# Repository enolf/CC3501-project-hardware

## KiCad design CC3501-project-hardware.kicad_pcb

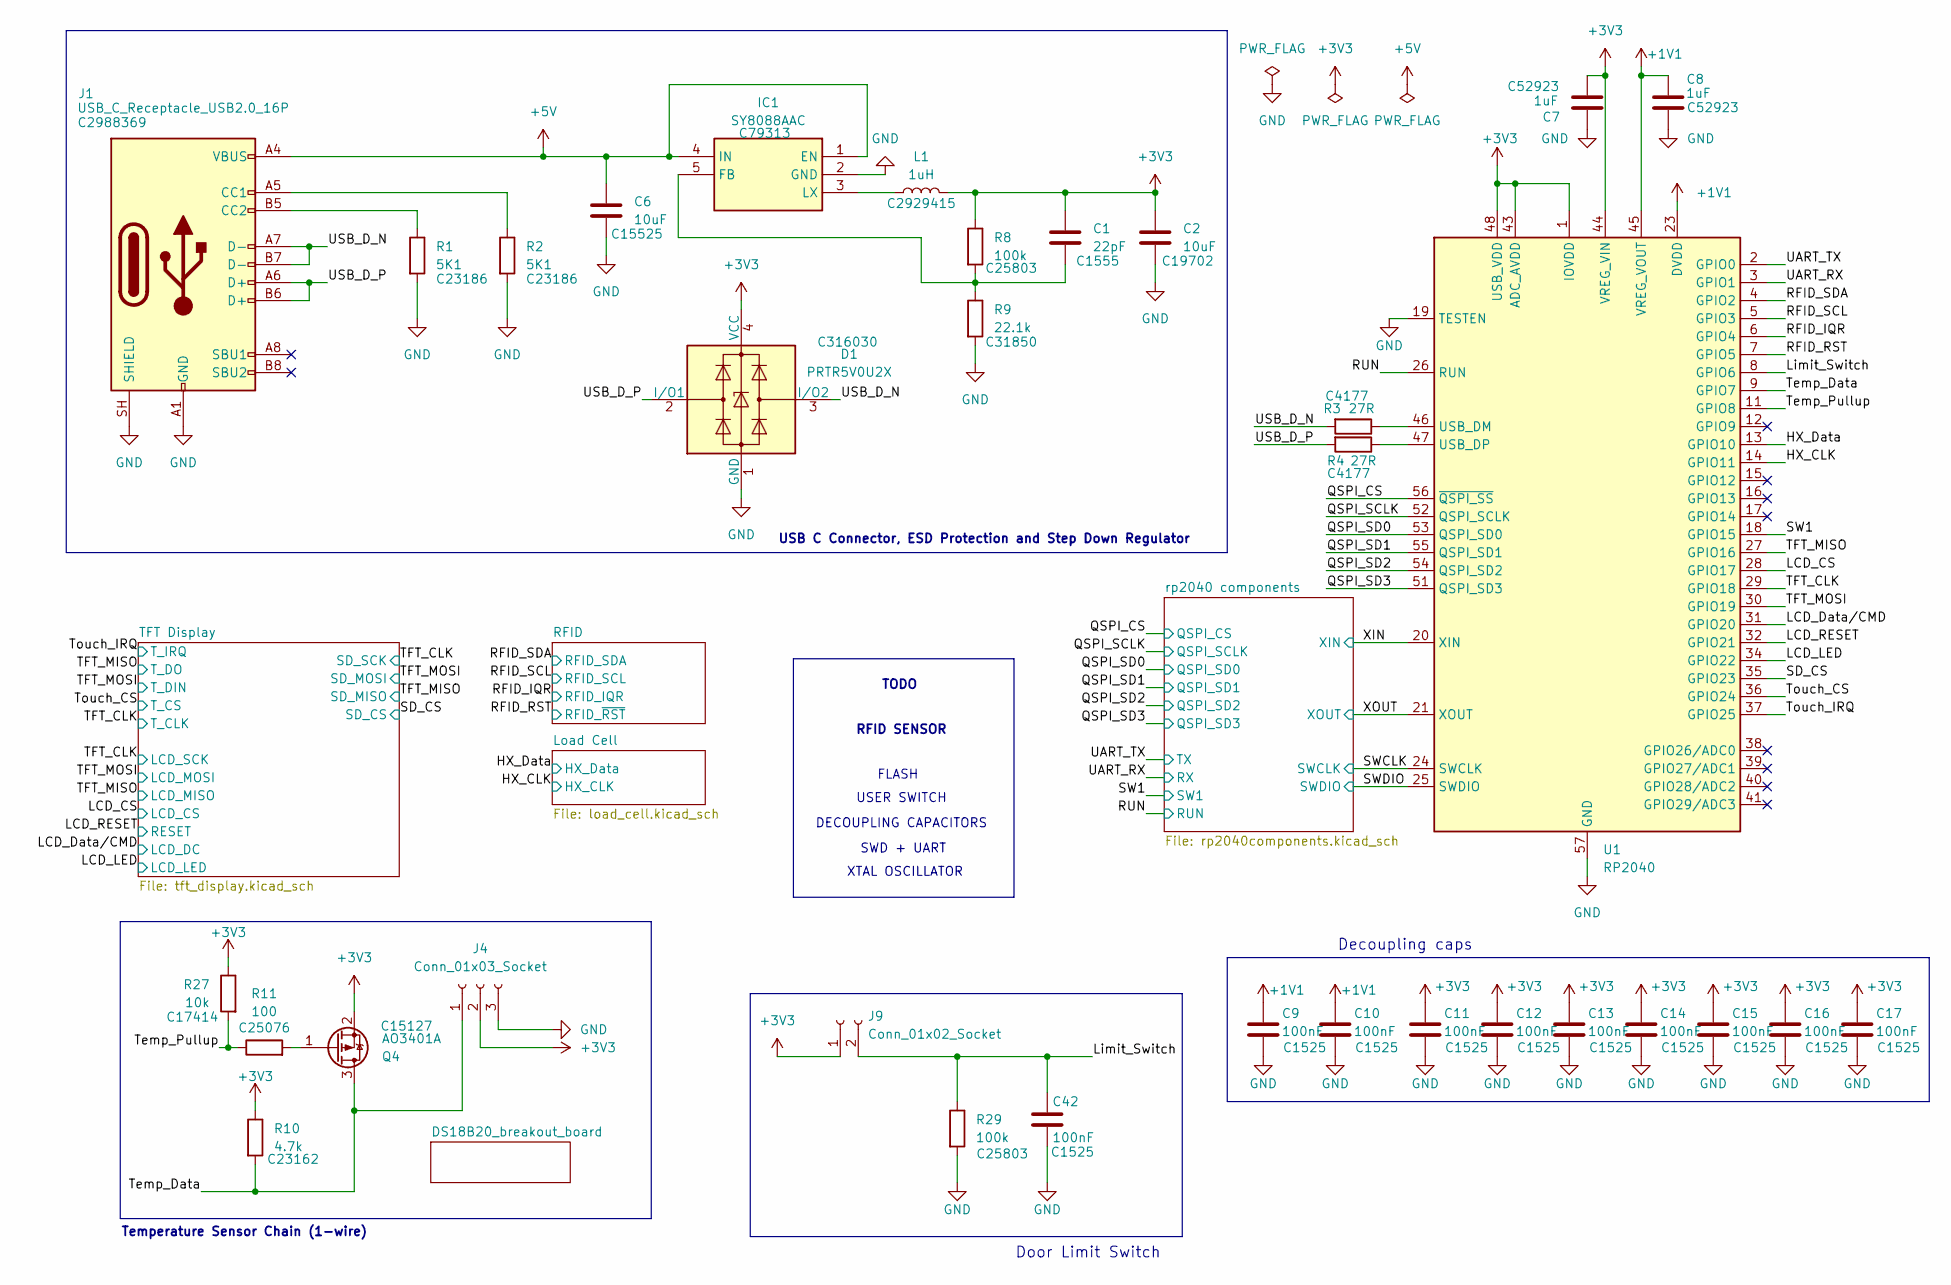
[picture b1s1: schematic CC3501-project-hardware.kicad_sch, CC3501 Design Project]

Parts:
C1: 22pF; C_0402_1005Metric; LCSC PN C1555
C2: 10uF; C_0603_1608Metric; LCSC PN C19702
C6: 10uF; C_0402_1005Metric; LCSC PN C15525
C7, C8: 1uF; C_0402_1005Metric; LCSC PN C52923
C9, C10, C11, C12, C13, C14, C15, C16, C17, C42: 100nF; C_0402_1005Metric; LCSC PN C1525
D1: PRTR5V0U2X; SOT-143; LCSC PN C316030
IC1: SY8088AAC; SOT95P285X140-5N; Manufacturer_Part_Number SY8088AAC
J1: USB_C_Receptacle_USB2.0_16P; USB_C_Receptacle_G-Switch_GT-USB-7010ASV; LCSC PN C2988369
J4: Conn_01x03_Socket; PinHeader_1x03_P2.54mm_Vertical
J9: Conn_01x02_Socket; PinHeader_1x02_P2.54mm_Vertical
L1: 1uH; IND-SMD_L4.5-W4.0; LCSC PN C2929415
Q4: AO3401A; SOT-23; LCSC PN C15127
R1, R2: 5K1; R_0201_0603Metric; LCSC PN C23186
R3, R4: 27R; R_0603_1608Metric; LCSC PN C4177
R8, R29: 100k; R_0603_1608Metric; LCSC PN C25803
R9: 22.1k; R_0603_1608Metric; LCSC PN C31850
R10: 4.7k; R_0603_1608Metric; LCSC PN C23162
R11: 100; R_0402_1005Metric; LCSC PN C25076
R27: 10k; R_0805_2012Metric; LCSC PN C17414
U1: RP2040; QFN-56-1EP_7x7mm_P0.4mm_EP3.2x3.2mm; LCSC PN C2040

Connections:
+1V1: C8.2, C9.1, C10.1, U1.23 (DVDD), U1.45 (VREG_VOUT), U1.50 (DVDD)
+5V: C6.1, IC1.1 (EN), IC1.4 (IN), J1.A4 (VBUS), J1.A9 (VBUS), J1.B4 (VBUS), J1.B9 (VBUS); also elsewhere on the board
/HX_CLK: U1.14 (GPIO11); also elsewhere on the board
/HX_Data: U1.13 (GPIO10); also elsewhere on the board
/LCD_CS: U1.28 (GPIO17); also elsewhere on the board
/LCD_Data/CMD: U1.31 (GPIO20); also elsewhere on the board
/LCD_LED: U1.34 (GPIO22); also elsewhere on the board
/LCD_RESET: U1.32 (GPIO21); also elsewhere on the board
/Limit_Switch: C42.1, J9.2, R29.1, U1.8 (GPIO6)
/QSPI_CS: U1.56 (~QSPI_SS); also elsewhere on the board
/QSPI_SCLK: U1.52 (QSPI_SCLK); also elsewhere on the board
/QSPI_SD0: U1.53 (QSPI_SD0); also elsewhere on the board
/QSPI_SD1: U1.55 (QSPI_SD1); also elsewhere on the board
/QSPI_SD2: U1.54 (QSPI_SD2); also elsewhere on the board
/QSPI_SD3: U1.51 (QSPI_SD3); also elsewhere on the board
/RFID_IQR: U1.6 (GPIO4); also elsewhere on the board
/RFID_RST: U1.7 (GPIO5); also elsewhere on the board
/RFID_SCL: U1.5 (GPIO3); also elsewhere on the board
/RFID_SDA: U1.4 (GPIO2); also elsewhere on the board
/RUN: U1.26 (RUN); also elsewhere on the board
/SD_CS: U1.35 (GPIO23); also elsewhere on the board
/SW1: U1.18 (GPIO15); also elsewhere on the board
/SWCLK: U1.24 (SWCLK); also elsewhere on the board
/SWDIO: U1.25 (SWDIO); also elsewhere on the board
/TFT_CLK: U1.29 (GPIO18); also elsewhere on the board
/TFT_MISO: U1.27 (GPIO16); also elsewhere on the board
/TFT_MOSI: U1.30 (GPIO19); also elsewhere on the board
/Temp_Data: J4.1, Q4.3 (D), R10.2, U1.9 (GPIO7)
/Temp_Pullup: R11.1, R27.2, U1.11 (GPIO8)
/Touch_CS: U1.36 (GPIO24); also elsewhere on the board
/Touch_IRQ: U1.37 (GPIO25); also elsewhere on the board
/USB_D_N: D1.3 (I/O2), J1.A7 (D-), J1.B7 (D-), R3.2
/USB_D_P: D1.2 (I/O1), J1.A6 (D+), J1.B6 (D+), R4.2
/XIN: U1.20 (XIN); also elsewhere on the board
/XOUT: U1.21 (XOUT); also elsewhere on the board
GND: C2.2, C6.2, C7.1, C8.1, C9.2, C10.2, C11.2, C12.2, C13.2, C14.2, C15.2, C16.2, C17.2, C42.2, D1.1 (GND), IC1.2 (GND), J1.A1 (GND), J1.A12 (GND), J1.B1 (GND), J1.B12 (GND), J1.SH (SHIELD), J4.3, R1.2, R2.2, R9.2, R29.2, U1.19 (TESTEN), U1.57 (GND); also elsewhere on the board
unnamed: C1.2, IC1.5 (FB), R8.2, R9.1
unnamed: IC1.3 (LX), L1.2
unnamed: J1.A5 (CC1), R2.1
unnamed: J1.B5 (CC2), R1.1
unnamed: Q4.1 (G), R11.2
unnamed: R3.1, U1.46 (USB_DM)
unnamed: R4.1, U1.47 (USB_DP)

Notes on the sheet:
TODO
FLASH
DECOUPLING CAPACITORS
Door Limit Switch
Decoupling caps
RFID SENSOR
SWD + UART
XTAL OSCILLATOR
USB C Connector, ESD Protection and Step Down Regulator
USER SWITCH
Temperature Sensor Chain (1-wire)

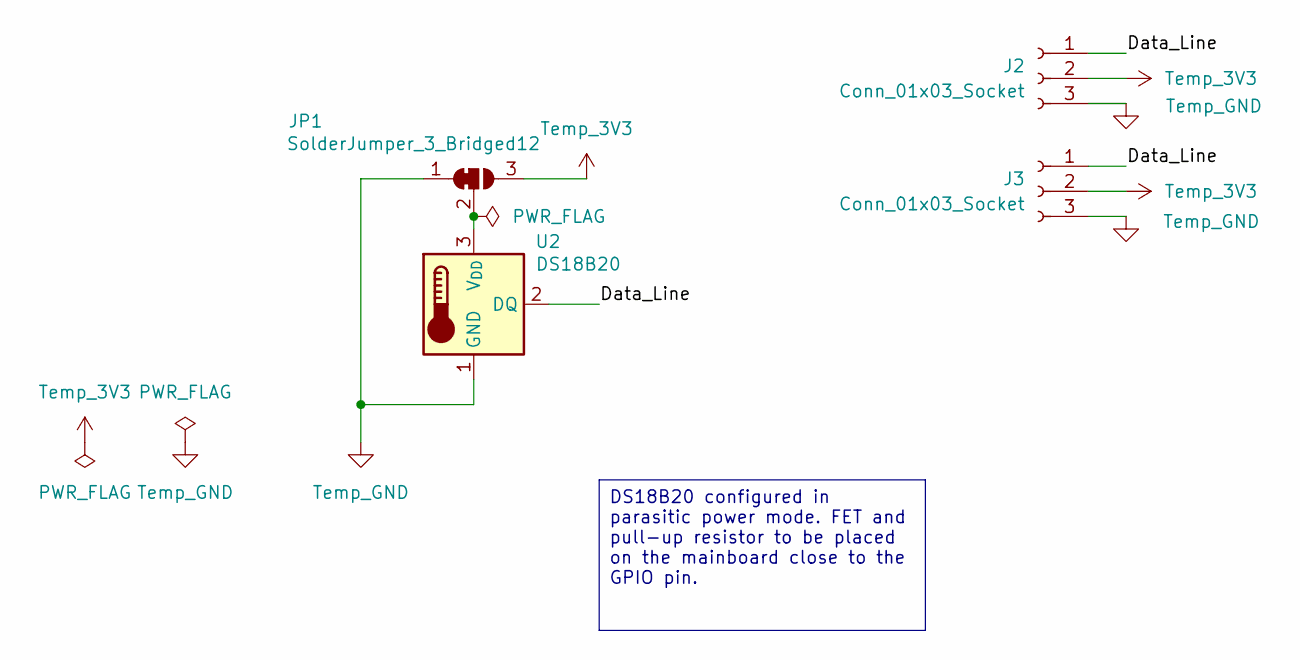
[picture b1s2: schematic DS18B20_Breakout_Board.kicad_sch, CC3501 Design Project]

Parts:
J2, J3: Conn_01x03_Socket; PinSocket_1x03_P2.54mm_Vertical
JP1: SolderJumper_3_Bridged12; SolderJumper-3_P1.3mm_Bridged12_RoundedPad1.0x1.5mm_NumberL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
U2: DS18B20; TO-92_Inline

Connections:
Temp_3V3: J2.2, J3.2, JP1.3 (B)

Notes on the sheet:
DS18B20 configured in parasitic power mode. FET and pull-up resistor to be placed on the mainboard close to the GPIO pin.

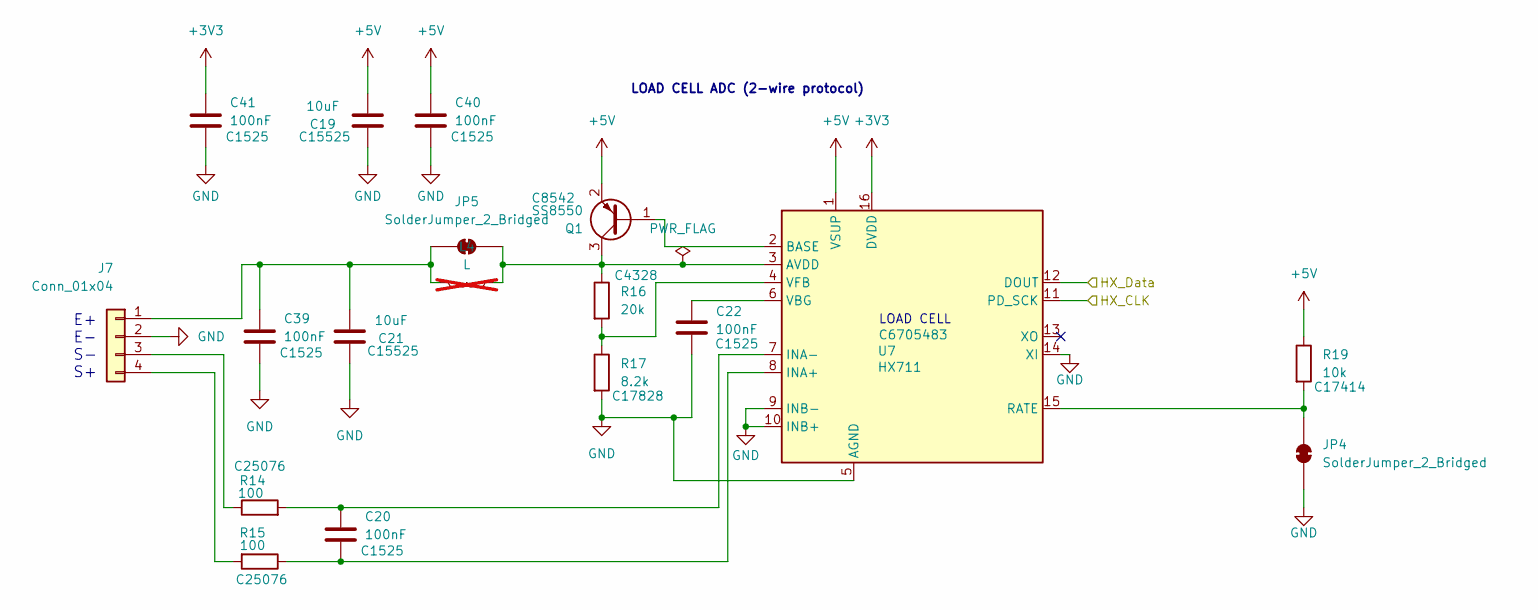
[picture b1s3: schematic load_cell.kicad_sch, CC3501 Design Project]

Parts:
C19, C21: 10uF; C_0402_1005Metric; LCSC PN C15525
C20, C22, C39, C40, C41: 100nF; C_0402_1005Metric; LCSC PN C1525
J7: Conn_01x04; PinHeader_1x04_P2.54mm_Vertical
JP4, JP5: SolderJumper_2_Bridged; SolderJumper-2_P1.3mm_Bridged2Bar_RoundedPad1.0x1.5mm
L4: L; L_Axial_L11.0mm_D4.5mm_P15.24mm_Horizontal_Fastron_MECC; not fitted
Q1: SS8550; SOT-23; LCSC PN C8542
R14, R15: 100; R_0402_1005Metric; LCSC PN C25076
R16: 20k; R_0805_2012Metric; LCSC PN C4328
R17: 8.2k; R_0805_2012Metric; LCSC PN C17828
R19: 10k; R_0805_2012Metric; LCSC PN C17414
U7: HX711; SOIC-16_3.9x9.9mm_P1.27mm; LCSC PN C6705483

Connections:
+5V: C19.2, C40.1, Q1.2 (E), R19.1, U7.1 (VSUP); also elsewhere on the board
/HX_CLK: U7.11 (PD_SCK); also elsewhere on the board
/HX_Data: U7.12 (DOUT); also elsewhere on the board
GND: C19.1, C21.1, C22.2, C39.2, C40.2, C41.2, J7.2, JP4.1 (A), R17.2, U7.5 (AGND), U7.9 (INB-), U7.10 (INB+), U7.14 (XI); also elsewhere on the board
unnamed: C21.2, C39.1, J7.1, JP5.2 (B), L4.1
unnamed: J7.3, R14.1
unnamed: J7.4, R15.2
unnamed: JP4.2 (B), R19.2, U7.15 (RATE)
unnamed: JP5.1 (A), L4.2, Q1.3 (C), R16.1, U7.3 (AVDD)
unnamed: Q1.1 (B), U7.2 (BASE)
unnamed: C20.2, R15.1, U7.8 (INA+)
unnamed: C20.1, R14.2, U7.7 (INA-)
unnamed: C22.1, U7.6 (VBG)
unnamed: R16.2, R17.1, U7.4 (VFB)

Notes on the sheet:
E+ E- S- S+
LOAD CELL ADC (2-wire protocol)
LOAD CELL

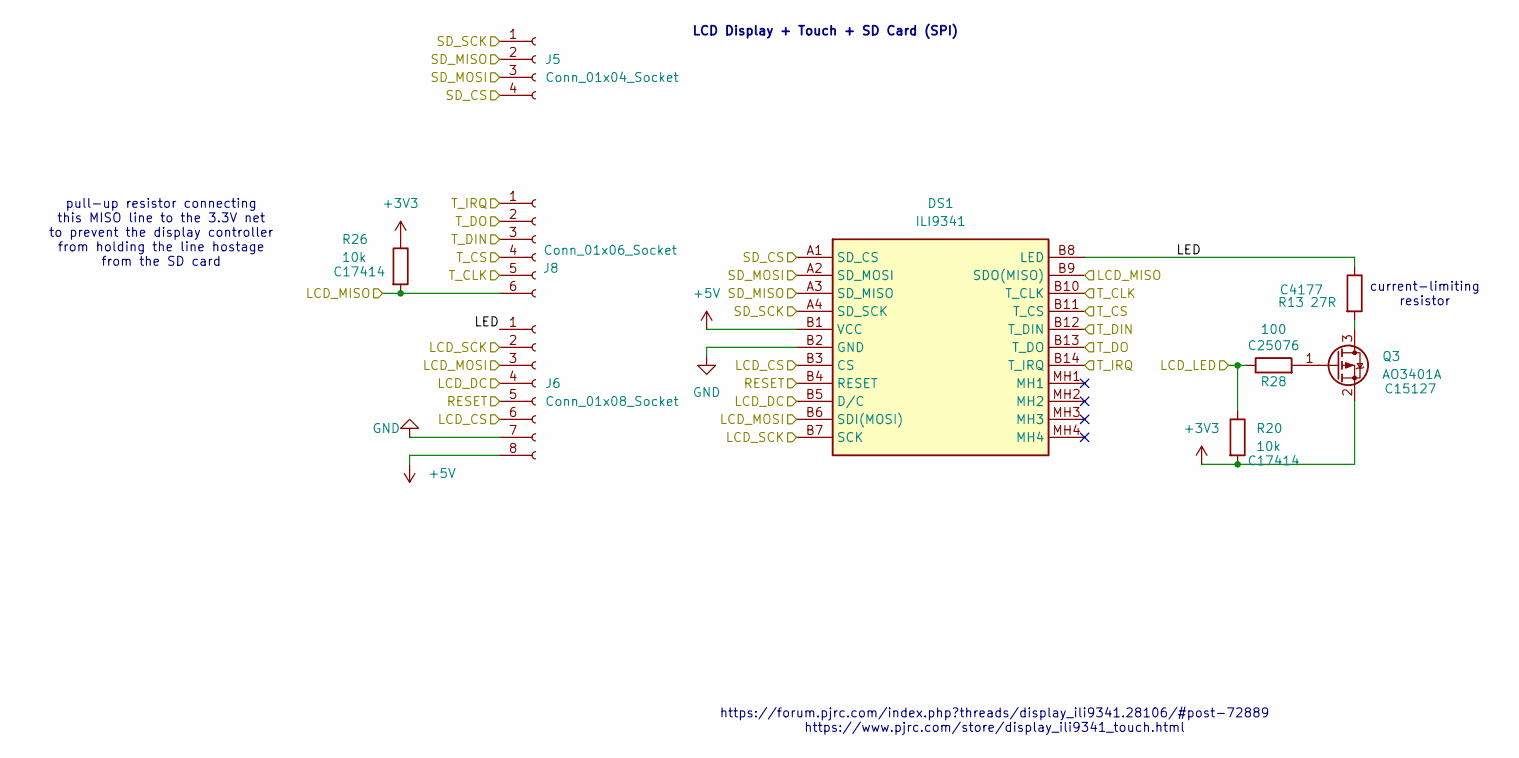
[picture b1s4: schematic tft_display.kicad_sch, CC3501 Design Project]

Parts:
DS1: ILI9341; Manufacturer_Part_Number ILI9341
J5: Conn_01x04_Socket; PinHeader_1x04_P2.54mm_Vertical
J6: Conn_01x08_Socket; PinHeader_1x08_P2.54mm_Vertical
J8: Conn_01x06_Socket; PinHeader_1x06_P2.54mm_Vertical
Q3: AO3401A; SOT-23; LCSC PN C15127
R13: 27R; R_0603_1608Metric; LCSC PN C4177
R20, R26: 10k; R_0805_2012Metric; LCSC PN C17414
R28: 100; R_0402_1005Metric; LCSC PN C25076

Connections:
+5V: DS1.B1 (VCC), J6.8; also elsewhere on the board
/LCD_CS: DS1.B3 (CS), J6.6; also elsewhere on the board
/LCD_Data/CMD: DS1.B5 (D/C), J6.4; also elsewhere on the board
/LCD_LED: R20.1, R28.1; also elsewhere on the board
/LCD_RESET: DS1.B4 (RESET), J6.5; also elsewhere on the board
/SD_CS: DS1.A1 (SD_CS), J5.4; also elsewhere on the board
/TFT Display/LED: DS1.B8 (LED), J6.1, R13.1
/TFT_CLK: DS1.A4 (SD_SCK), DS1.B7 (SCK), DS1.B10 (T_CLK), J5.1, J6.2, J8.5; also elsewhere on the board
/TFT_MISO: DS1.A3 (SD_MISO), DS1.B9 (SDO(MISO)), DS1.B13 (T_DO), J5.2, J8.2, J8.6, R26.2; also elsewhere on the board
/TFT_MOSI: DS1.A2 (SD_MOSI), DS1.B6 (SDI(MOSI)), DS1.B12 (T_DIN), J5.3, J6.3, J8.3; also elsewhere on the board
/Touch_CS: DS1.B11 (T_CS), J8.4; also elsewhere on the board
/Touch_IRQ: DS1.B14 (T_IRQ), J8.1; also elsewhere on the board
GND: DS1.B2 (GND), J6.7; also elsewhere on the board
unnamed: Q3.3 (D), R13.2
unnamed: Q3.1 (G), R28.2

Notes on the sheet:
LCD Display + Touch + SD Card (SPI)
https://forum.pjrc.com/index.php?threads/display_ili9341.28106/#post-72889 https://www.pjrc.com/store/display_ili9341_touch.html
current-limiting resistor
pull-up resistor connecting this MISO line to the 3.3V net to prevent the display controller from holding the line hostage from the SD card

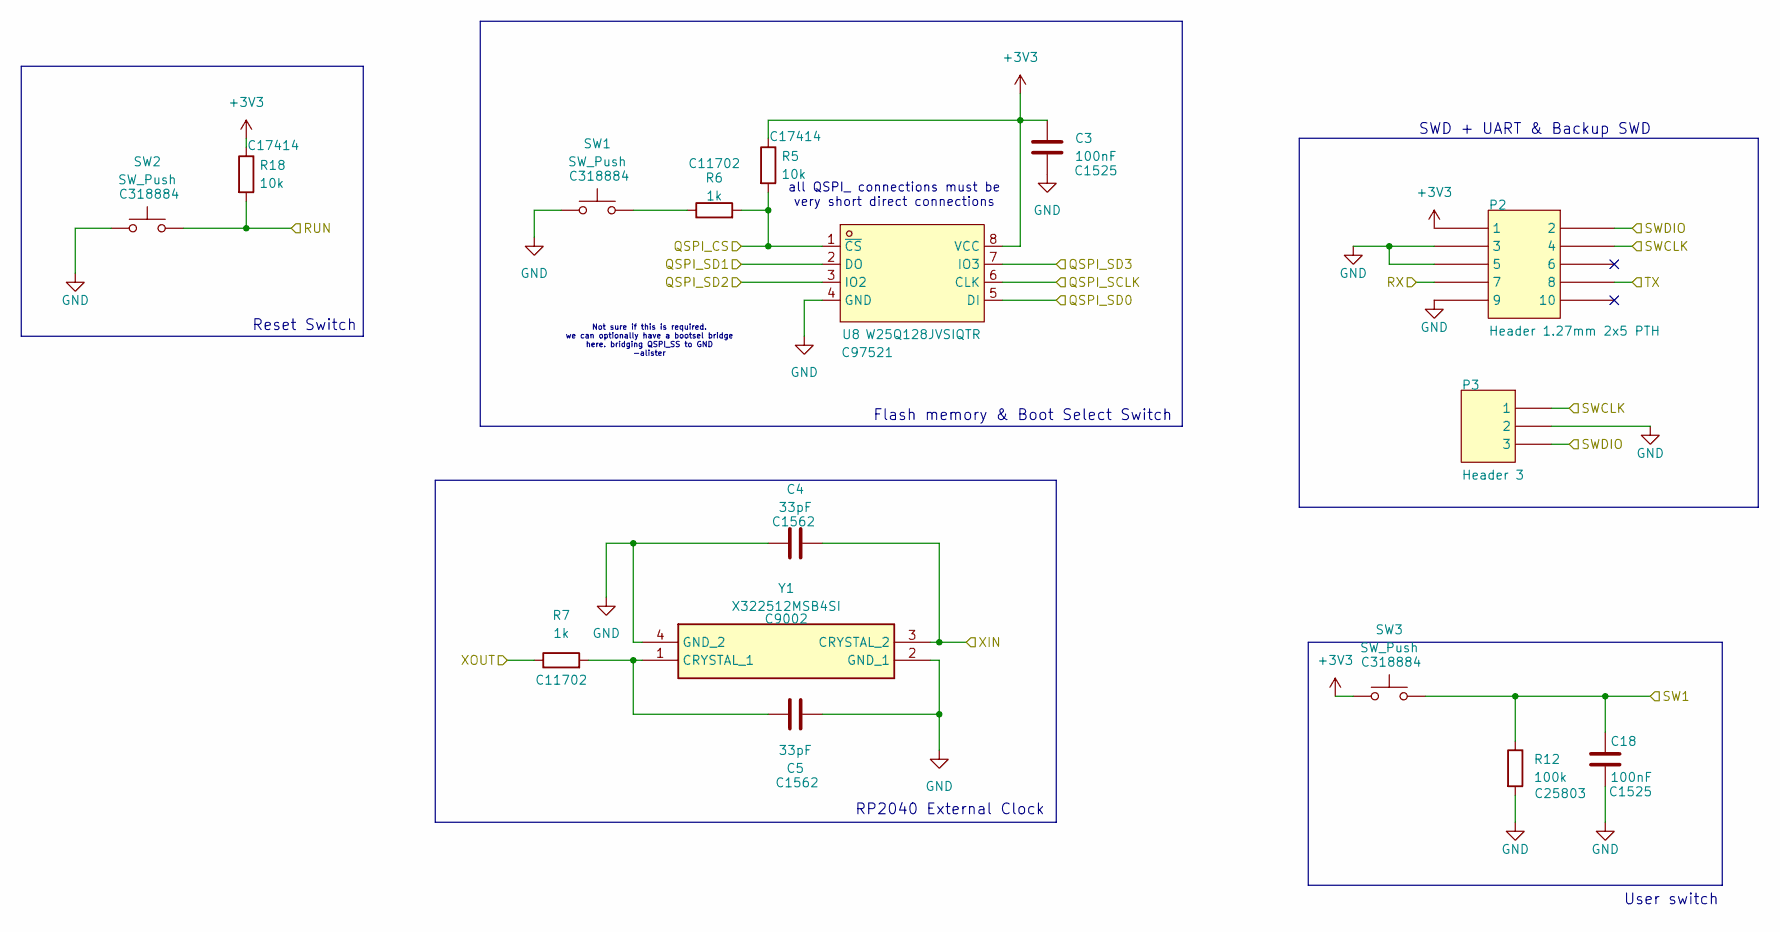
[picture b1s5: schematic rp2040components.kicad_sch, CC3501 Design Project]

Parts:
C3, C18: 100nF; C_0402_1005Metric; LCSC PN C1525
C4, C5: 33pF; C_0402_1005Metric; LCSC PN C1562
P2: Header 1.27mm 2x5 PTH; PinHeader_2x05_P1.27mm_Vertical
P3: Header 3; PinHeader_1x03_P2.54mm_Vertical
R5, R18: 10k; R_0805_2012Metric; LCSC PN C17414
R6, R7: 1k; R_0402_1005Metric; LCSC PN C11702
R12: 100k; R_0603_1608Metric; LCSC PN C25803
SW1, SW2, SW3: SW_Push; SW_SPST_Omron_B3F-40xx; LCSC PN C318884
U8: W25Q128JVSIQTR; SOIC-8_L5.3-W5.3-P1.27-LS8.0-BL; MPN W25Q128JVSIQ; LCSC PN C97521
Y1: X322512MSB4SI; Crystal_SMD_TXC_7M-4Pin_3.2x2.5mm; Manufacturer_Part_Number X322512MSB4SI; LCSC PN C9002

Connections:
/QSPI_CS: R5.2, R6.2, U8.1 (~CS); also elsewhere on the board
/QSPI_SCLK: U8.6 (CLK); also elsewhere on the board
/QSPI_SD0: U8.5 (DI); also elsewhere on the board
/QSPI_SD1: U8.2 (DO); also elsewhere on the board
/QSPI_SD2: U8.3 (IO2); also elsewhere on the board
/QSPI_SD3: U8.7 (IO3); also elsewhere on the board
/RUN: R18.2, SW2.2; also elsewhere on the board
/SW1: C18.1, R12.1, SW3.2; also elsewhere on the board
/SWCLK: P2.4, P3.1; also elsewhere on the board
/SWDIO: P2.2, P3.3; also elsewhere on the board
/XIN: C4.1, Y1.3 (CRYSTAL_2); also elsewhere on the board
/XOUT: R7.1; also elsewhere on the board
GND: C3.2, C4.2, C5.2, C18.2, P2.3, P2.5, P2.9, P3.2, R12.2, SW1.1, SW2.1, U8.4 (GND), Y1.2 (GND_1), Y1.4 (GND_2); also elsewhere on the board
unnamed: R6.1, SW1.2
unnamed: C5.1, R7.2, Y1.1 (CRYSTAL_1)

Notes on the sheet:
Flash memory & Boot Select Switch
RP2040 External Clock
Reset Switch
SWD + UART & Backup SWD
Not sure if this is required. we can optionally have a bootsel bridge here. bridging QSPI_SS to GND -alister
User switch
all QSPI_ connections must be very short direct connections

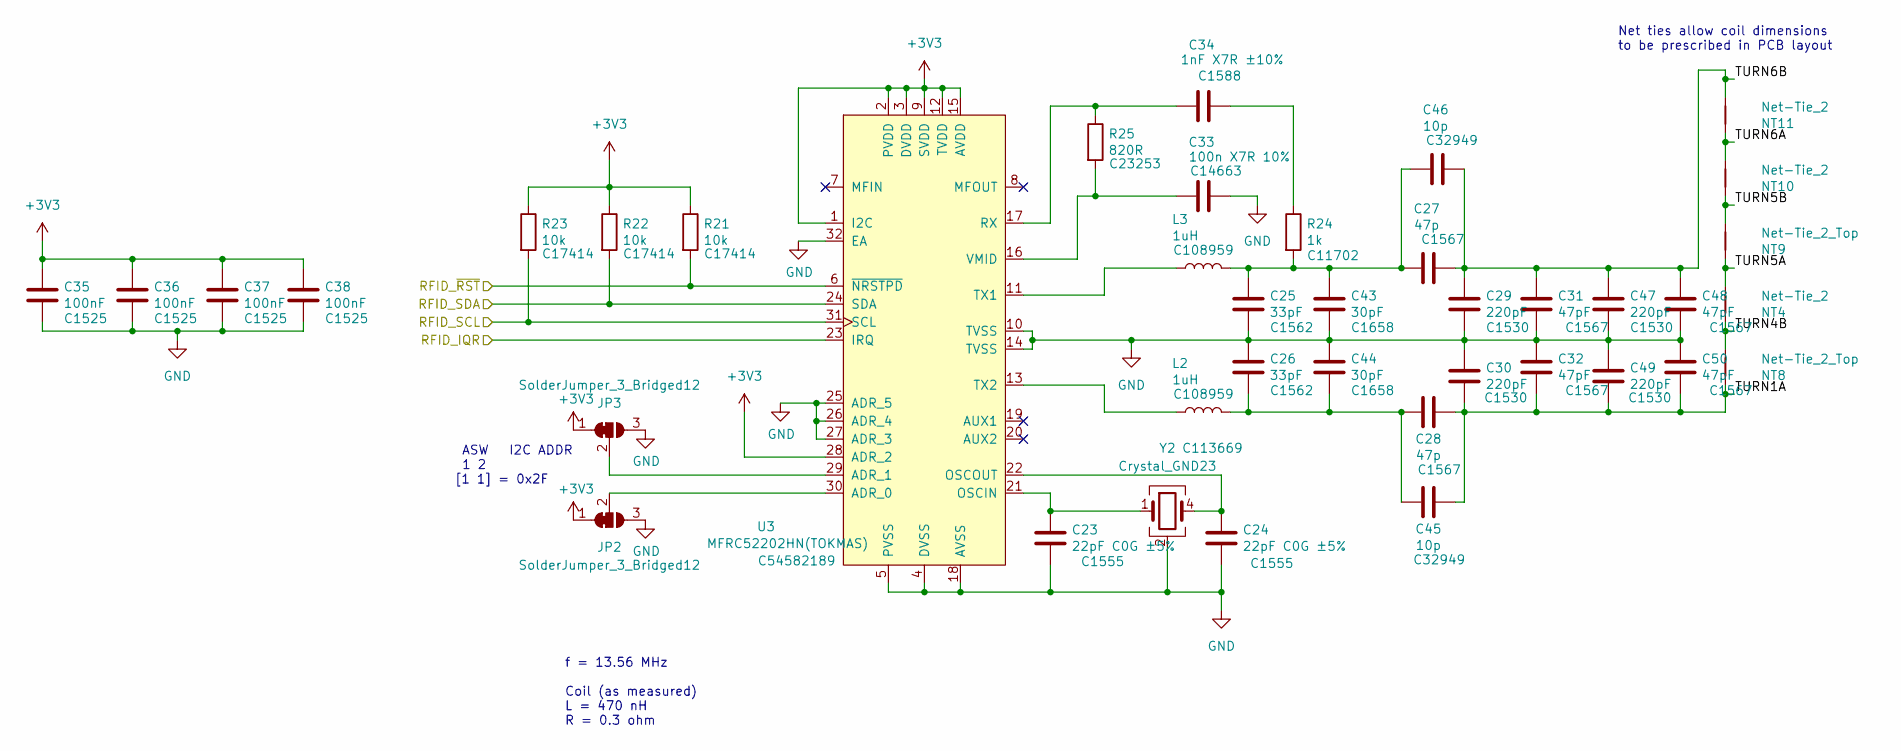
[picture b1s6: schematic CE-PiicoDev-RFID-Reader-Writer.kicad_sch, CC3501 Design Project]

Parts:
C23, C24: 22pF C0G ±5%; C_0402_1005Metric; LCSC PN C1555
C25, C26: 33pF; C_0402_1005Metric; LCSC PN C1562
C27, C28: 47p; C_0402_1005Metric; LCSC PN C1567
C29, C30, C47, C49: 220pF; C_0402_1005Metric; LCSC PN C1530
C31, C32, C48, C50: 47pF; C_0402_1005Metric; LCSC PN C1567
C33: 100n X7R 10%; C_0603_1608Metric; LCSC PN C14663
C34: 1nF X7R ±10%; C_0603_1608Metric; LCSC PN C1588
C35, C36, C37, C38: 100nF; C_0402_1005Metric; LCSC PN C1525
C43, C44: 30pF; C_0201_0603Metric; LCSC PN C1658
C45, C46: 10p; C_0402_1005Metric; LCSC PN C32949
JP2, JP3: SolderJumper_3_Bridged12; SolderJumper-3_P1.3mm_Bridged12_RoundedPad1.0x1.5mm_NumberL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
L2, L3: 1uH; L_0805_2012Metric; LCSC PN C108959
NT4, NT10, NT11: Net-Tie_2; NetTie-2_SMD_Pad0.80mm
NT8, NT9: Net-Tie_2_Top; NetTie-2_SMD_Pad0.80mm
R21, R22, R23: 10k; R_0805_2012Metric; LCSC PN C17414
R24: 1k; R_0402_1005Metric; LCSC PN C11702
R25: 820R; R_0603_1608Metric; LCSC PN C23253
U3: MFRC52202HN(TOKMAS); VQFN-32-1EP_5x5mm_P0.5mm_EP3.1x3.1mm_ThermalVias; LCSC PN C54582189
Y2: Crystal_GND23; Crystal_SMD_3225-4Pin_3.2x2.5mm; LCSC PN C113669

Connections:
/RFID/TURN1A: C28.1, C30.2, C32.2, C45.1, C49.2, C50.2, NT8.1
/RFID/TURN6B: C27.1, C29.1, C31.1, C46.1, C47.1, C48.1, NT11.2
/RFID_IQR: U3.23 (IRQ); also elsewhere on the board
/RFID_RST: R21.2, U3.6 (~NRSTPD); also elsewhere on the board
/RFID_SCL: R23.2, U3.31 (SCL); also elsewhere on the board
/RFID_SDA: R22.2, U3.24 (SDA); also elsewhere on the board
/TURN4B: NT4.1, NT8.2
/TURN5A: NT4.2, NT9.1
/TURN5B: NT9.2, NT10.1
/TURN6A: NT10.2, NT11.1
GND: C23.2, C24.2, C25.2, C26.1, C29.2, C30.1, C31.2, C32.1, C33.1, C35.2, C36.2, C37.2, C38.2, C43.2, C44.1, C47.2, C48.2, C49.1, C50.1, JP2.3 (B), JP3.3 (B), U3.4 (DVSS), U3.5 (PVSS), U3.10 (TVSS), U3.14 (TVSS), U3.18 (AVSS), U3.25 (ADR_5), U3.26 (ADR_4), U3.27 (ADR_3), U3.32 (EA), Y2.2 (G), Y2.3 (G); also elsewhere on the board
unnamed: C25.1, C27.2, C43.1, C46.2, L3.2, R24.2
unnamed: C26.2, C28.2, C44.2, C45.2, L2.2
unnamed: C34.1, R24.1
unnamed: JP2.2 (C), U3.30 (ADR_0)
unnamed: JP3.2 (C), U3.29 (ADR_1)
unnamed: C23.1, U3.21 (OSCIN), Y2.1
unnamed: C24.1, U3.22 (OSCOUT), Y2.4
unnamed: C34.2, R25.1, U3.17 (RX)
unnamed: L3.1, U3.11 (TX1)
unnamed: L2.1, U3.13 (TX2)
unnamed: C33.2, R25.2, U3.16 (VMID)

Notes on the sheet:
ASW I2C ADDR 1 2 [1 1] = 0x2F
f = 13.56 MHz Coil (as measured) L = 470 nH R = 0.3 ohm
Net ties allow coil dimensions to be prescribed in PCB layout

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
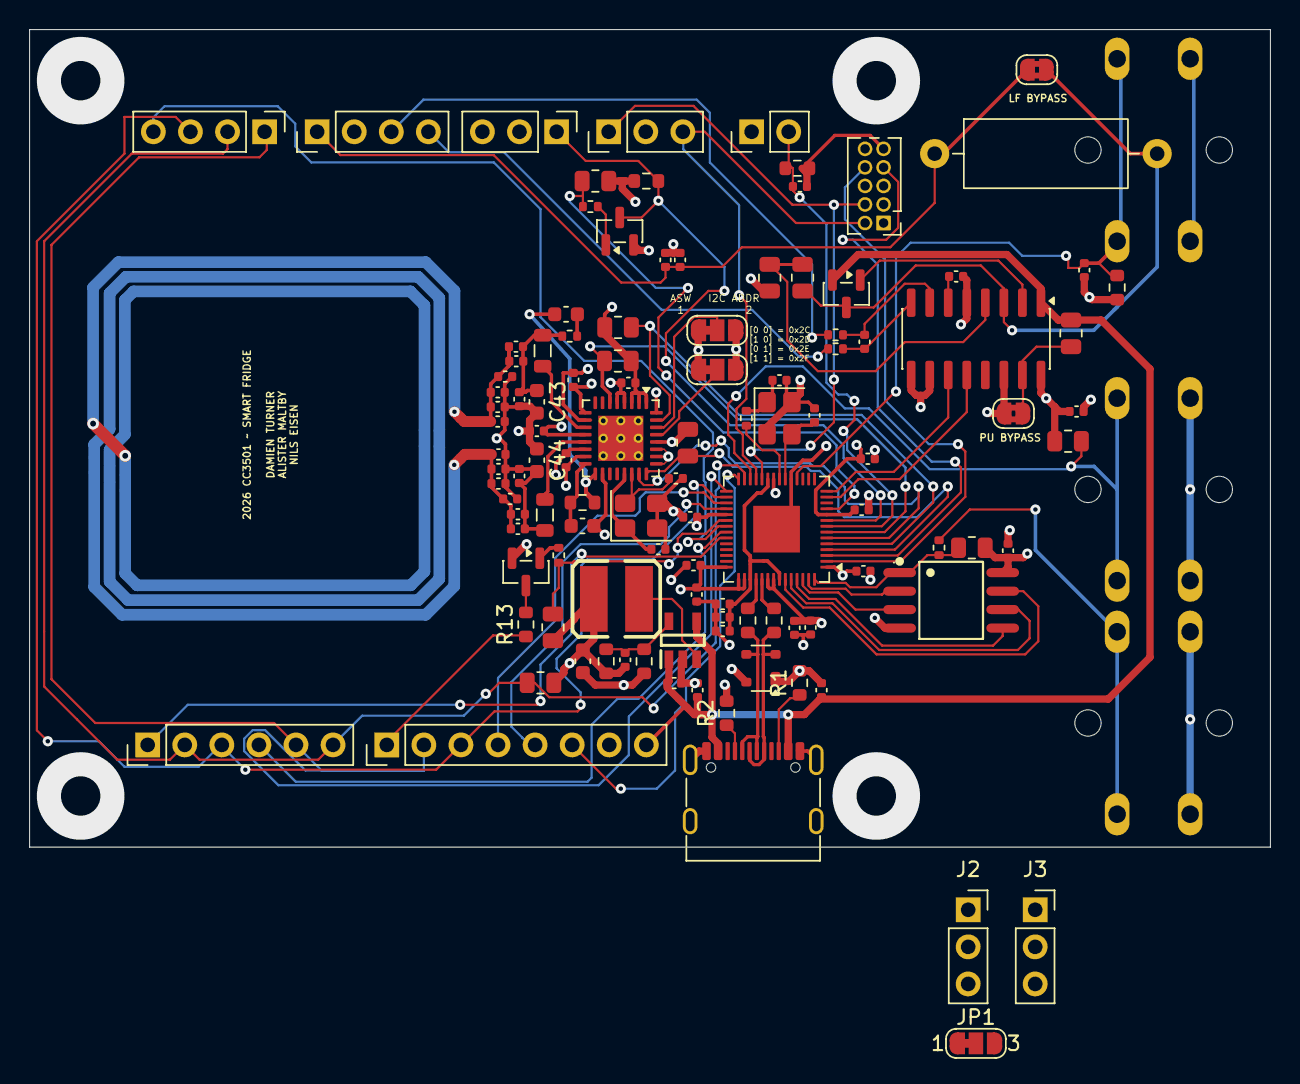
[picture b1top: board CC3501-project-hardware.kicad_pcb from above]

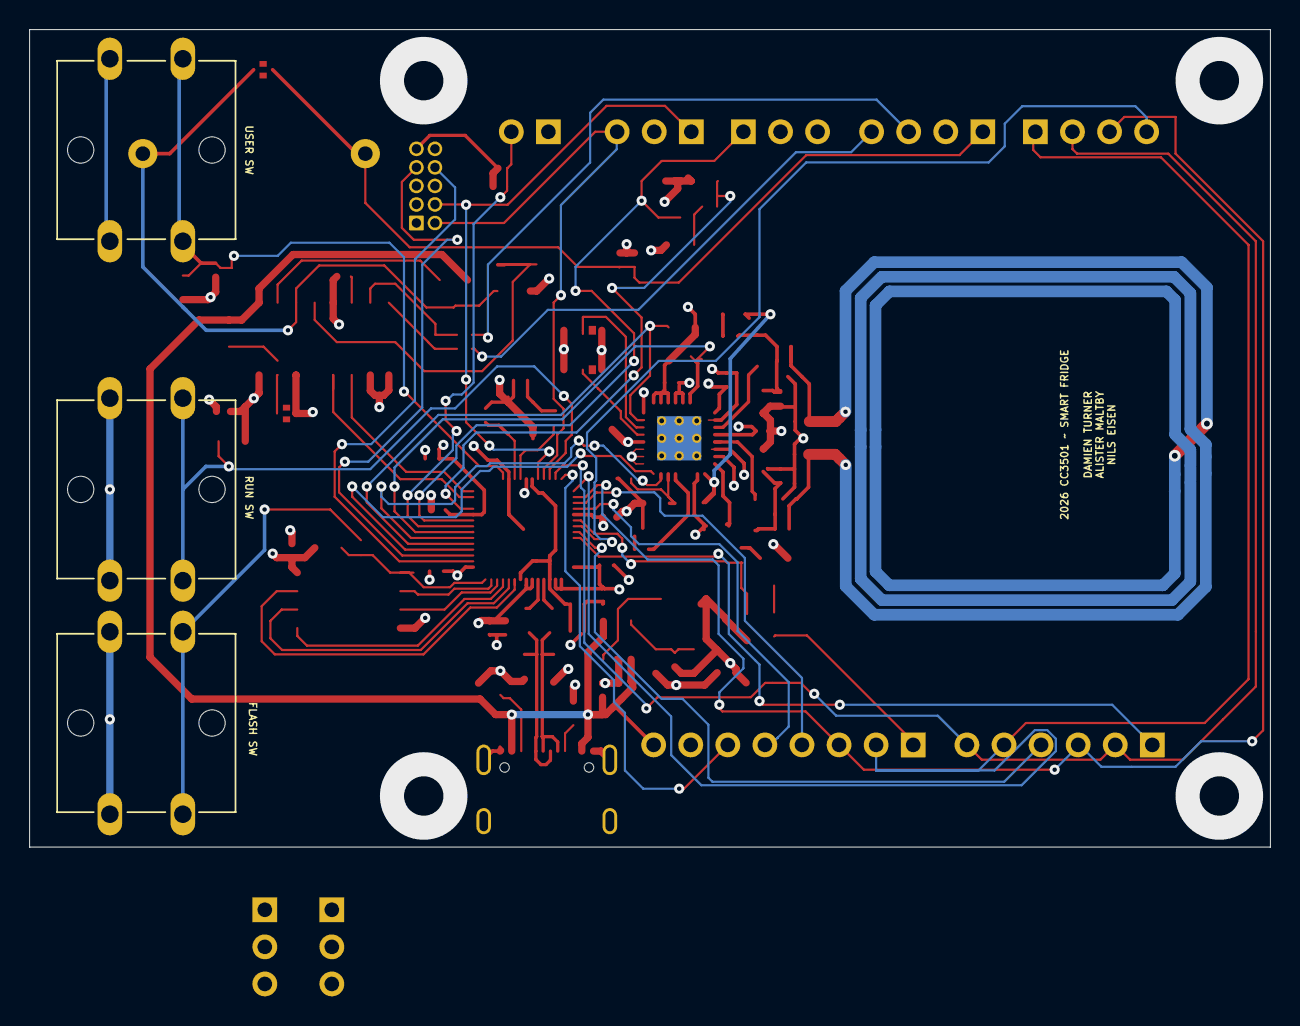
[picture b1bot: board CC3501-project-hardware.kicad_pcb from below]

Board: 4 copper layers, 85.0 x 56.0 mm, 118 parts (8 on the bottom side), 80 nets.

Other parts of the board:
U4: SY8089A1AAC; SOT95P285X130-5N

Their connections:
+5V: U4.1 (EN), U4.4 (IN); also elsewhere on the board
GND: U4.2 (GND); also elsewhere on the board

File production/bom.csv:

Designator,Footprint,Quantity,Value,LCSC Part #
C1,0402,1,22pF,C1555
"C10, C11, C12, C13, C14, C15, C16, C17, C18, C20, C22, C3, C35, C36, C37, C38, C39, C40, C41, C42, C9",0402,21,100nF,C1525
"C19, C21, C6",0402,3,10uF,C15525
C2,0603,1,10uF,C19702
C23,0402,1,22pF C0G ±5%,C1555
C24,0402,1,22pF C0G ±5%,C1555 
"C25, C26",0805,2,62p NP0 2%,C520069
"C27, C28",0603,2,56p,C107053
"C29, C30, C31, C32",0603,4,270p NP0 2%,C327196
C33,0603,1,100n X7R 10%,C14663
C34,0603,1,1nF X7R ±10%,C1588
"C4, C5",0402,2,33pF,C1562
"C7, C8",0402,2,1uF,C52923
D1,SOT-143,1,PRTR5V0U2X,C316030
G1,piicodev_logo_14.2x3.4mm,1,LOGO_PiicoDev,
G7,Art_2,1,Label_PCB_Art,
J1,USB_C_Receptacle_G-Switch_GT-USB-7010ASV,1,USB_C_Receptacle_USB2.0_16P,C2988369 
J4,PinHeader_1x03_P2.54mm_Vertical,1,Conn_01x03_Socket,
J5,PinHeader_1x04_P2.54mm_Vertical,1,Conn_01x04_Socket,
J6,PinHeader_1x08_P2.54mm_Vertical,1,Conn_01x08_Socket,
J7,PinHeader_1x04_P2.54mm_Vertical,1,Conn_01x04,
J8,PinHeader_1x06_P2.54mm_Vertical,1,Conn_01x06_Socket,
J9,PinHeader_1x02_P2.54mm_Vertical,1,Conn_01x02_Socket,
L1,IND-SMD_L4.5-W4.0,1,1uH,C2929415
"L2, L3",0805,2,1uH,C108959
L4,0805,1,10uH,C1046 
Q1,SOT-23,1,SS8550,C8542
"Q3, Q4",SOT-23,2,AO3401A,C15127
"R1, R2",0201,2,5K1,C23186
R10,0603,1,4.7k,C23162
"R11, R14, R15, R28",0402,4,100,C25076
"R12, R29",0201,2,100k,C25803 
R13,0201,1,27R,C25190
R16,0805,1,20k,C4328
R17,0805,1,8.2k,C17828
"R18, R19, R20, R21, R22, R23, R26, R27, R5",0805,9,10k,C17414
"R24, R6, R7",0402,3,1k,C11702
R25,0603,1,820R,C23253
"R3, R4",0603,2,27R,C25190
R8,0603,1,100k,C25803
R9,0603,1,22.1k,C31850
"SW1, SW2, SW3",SW_Push_1P1T_XKB_TS-1187A,3,SW_Push,C318884
U1,QFN-56-1EP_7x7mm_P0.4mm_EP3.2x3.2mm,1,RP2040,C2040
U3,VQFN-32-1EP_5x5mm_P0.5mm_EP3.1x3.1mm_ThermalVias,1,MFRC522,C54582189
U4,SOT95P285X130-5N,1,SY8089A1AAC,C479074
U7,SOIC-16_3.9x9.9mm_P1.27mm,1,HX711,C6705483
U8,SOIC-8_L5.3-W5.3-P1.27-LS8.0-BL,1,W25Q128JVSIQTR,C97521
Y1,Crystal_SMD_TXC_7M-4Pin_3.2x2.5mm,1,X322512MSB4SI,C9002
Y2,Crystal_SMD_3225-4Pin_3.2x2.5mm,1,Crystal_GND23,C113669

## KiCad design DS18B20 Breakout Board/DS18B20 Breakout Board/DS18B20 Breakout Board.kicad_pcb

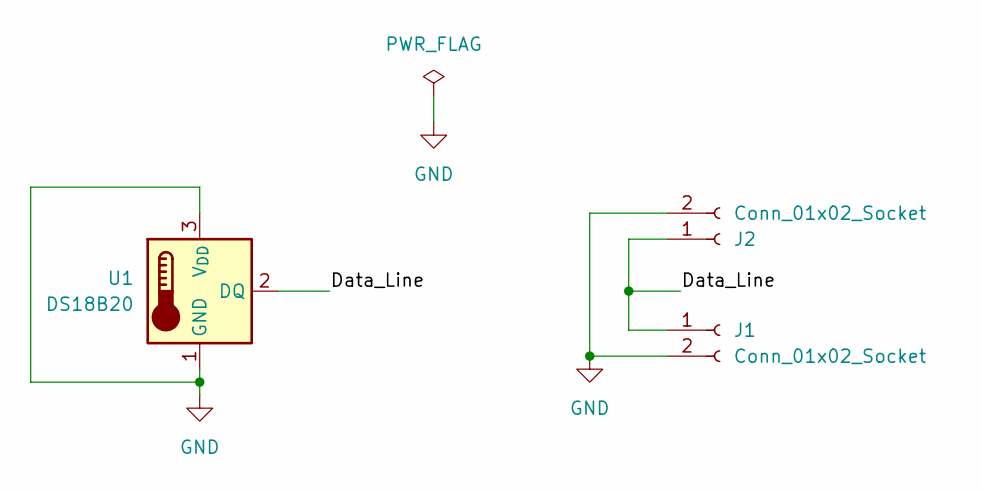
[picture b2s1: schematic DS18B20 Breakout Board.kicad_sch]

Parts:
J1, J2: Conn_01x02_Socket; PinHeader_1x02_P2.54mm_Vertical
U1: DS18B20; TO-92_Inline

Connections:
/Data_Line: J1.1, J2.1, U1.2 (DQ)
GND: J1.2, J2.2, U1.1 (GND), U1.3 (V_{DD})

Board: 2 copper layers, 3 parts (0 on the bottom side), 2 nets, no tracks yet.

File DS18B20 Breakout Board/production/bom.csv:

Designator,Footprint,Quantity,Value,LCSC Part #
"J1, J2",PinHeader_1x02_P2.54mm_Vertical,2,Conn_01x02_Socket,
U1,TO-92_Inline,1,DS18B20,

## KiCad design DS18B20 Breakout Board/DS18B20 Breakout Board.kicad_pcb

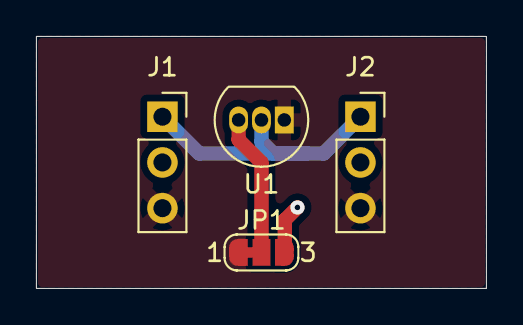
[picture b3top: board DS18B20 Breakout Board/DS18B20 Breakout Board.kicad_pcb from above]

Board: 2 copper layers, 25.0 x 14.0 mm, 4 parts (0 on the bottom side), 4 nets.

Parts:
J1, J2: Conn_01x03_Socket; PinSocket_1x03_P2.54mm_Vertical
JP1: SolderJumper_3_Bridged12; SolderJumper-3_P1.3mm_Bridged12_RoundedPad1.0x1.5mm_NumberL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
U1: DS18B20; TO-92_Inline

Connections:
+3V3: J1.2, J2.2, JP1.3 (B)
/Data_Line: J1.1, J2.1, U1.2 (DQ)
GND: J1.3, J2.3, JP1.1 (A), U1.1 (GND)
unnamed: JP1.2 (C), U1.3 (V_{DD})

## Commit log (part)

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2026-06-08 Add gitignore
2026-06-08 Untrack backup
2026-06-09 Add RP2040 and DS18B20
2026-06-09 Wire up temp sensor wrong.
2026-06-09 Undo wrong wiring.
2026-06-09 Internal KiCAD test edits.
2026-06-09 Make a wiring change.
2026-06-13 Force push.
2026-06-13 Fresh start.
2026-06-13 Add USB C and make connections to ground.
2026-06-13 Add voltage regulator to USB input.
2026-06-14 Add connection from USB DN/DP pins to RP2040 and include series 27R resisotor.
2026-06-14 Added LCD, Load Cell Amplifier and Temp Sensors to schematic and made connections to RP2040.
2026-06-15 Add JLC part number to HX711
2026-06-15 Add annotations for future considerations.
2026-06-15 Added lcsc lib and changed gitignore
2026-06-15 Flash added to sch
2026-06-15 Clock added
2026-06-16 Revert "Merge branch 'master' of https://github.com/enolf/CC3501-project-hardware"
    This reverts commit 2500d5ad2e3feed9fc5dfb9bd824a4702660caf9, reversing
    changes made to 56ed78568c6556d2d0023d84cb985b4cc09a45fd.
2026-06-16 Reapply "Merge branch 'master' of https://github.com/enolf/CC3501-project-hardware"
    This reverts commit 1f4ff7fa30b99a2d4c13749025865a9144c5015b.
2026-06-16 Create schematic and PCB for DS18B20 breakout board
2026-06-16 Add 3D model file, fixed pathing, checked final PCB model and generated fab files.
2026-06-16 add design note about FET and pull-up resistor, based on peer-review feedback.
2026-06-16 Added a seperate page for rp2040 required parts
2026-06-16 testing 2nd page
2026-06-16 Renamed page 2
2026-06-17 Move DS18B20 breakout board into schematic.
2026-06-17 Remove previous DS18B20 file.
2026-06-17 add new dc-dc converter with recommended circuit layout for 3.3v
2026-06-17 finalise dc-dc step down.
2026-06-17 Add JLC part numbers, button and correct oscillator to Page 2
2026-06-17 add temp sensor pull up fet and pull up resistor
2026-06-17 add a whole bunch off stuff
    - separated TFT display and HX711 into separate pages
    - add ESD protection resistor to temp sensor
    - corrected/added various JLC PCB part numbers
    - swapped oscillator for the one used in part 1
    - moved blocks of schematic around and into other pages to neaten it all up
    - added file with download footprints, symbols, and 3D models
2026-06-18 Add RFID schem.
2026-06-18 Add RFID circuit.
2026-06-18 added most circuit to HX711 sch
2026-06-18 reconfigure DS18B20 breakout board
    - Change JST from 2-pin to 3-pin
    - Add a solder jumper for switching between parasitic and external power
2026-06-18 Breakout Board, ESD protection and TFT display updates
2026-06-18 Finished HX711
2026-06-19 Import RFID module from Core Electronics
2026-06-19 Link RFID Module to board.
2026-06-19 Clean up RFID module.
2026-06-19 Removed wrong part numbers field.
2026-06-19 Renamed duplicate references.
2026-06-19 Attached part number to components.
2026-06-19 Add footprint to xtal oscillator.
2026-06-20 Fix ERC errors.
2026-06-20 Remove duplicated power flag.
2026-06-20 Change wiring on temp sensor.
2026-06-20 Rewire TFT display to power with 5V and allowing backlight switching via FET.
2026-06-20 update passive power FET from N-CH to P-CH as recommended from peer review.
2026-06-20 edit HX711 config
2026-06-20 edit HX711 configuration to match datasheet and sparkfun example as well as add JLC part numbers and display them on schematic
2026-06-21 Add part numbers for USB C and RFID xtal.
2026-06-21 Add reset switch to RUN pin.
2026-06-21 Revert to autosave.
2026-06-21 Add symbol/footprint library linkages.
2026-06-21 Add PCB with JLC config from assignment 1 pt 1.
2026-06-21 Add layout drawings for PCB.
2026-06-21 Recover autosave.
2026-06-21 Add JLC part number for voltage reg
2026-06-21 Layout the RP2040 basic components.
2026-06-21 swapped around TFT pinout to match physical board
2026-06-21 add 100ohm current limit resistor to TFT LED GPIO control pin
2026-06-21 add door limit switch connector and hardware debounce.
2026-06-21 Update sheet naming
2026-06-21 add boxes around system blocks with labels
2026-06-21 Create DS18B20 Breakout Board Zip
2026-06-21 Assemble board.
2026-06-21 Add edgecuts.
2026-06-21 Generate production files.
2026-06-22 swapped voltage rep for potential alternative
2026-06-22 ALL the PCB edits.
2026-06-24 changed component footprint
2026-06-24 updated R1,R2 position on pcb
2026-06-24 finished C43 and C44 and poured with b
2026-06-24 Fixed 3v3 gnd cap near RFID

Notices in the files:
RFID/CE-PiicoDev-RFID-Reader-Writer.kicad_sch:
License: CCASAv4.0 http://creativecommons.org/licenses/by-sa/4.0
